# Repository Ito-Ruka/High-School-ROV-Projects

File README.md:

# High-Current ESC Carrier & Power Distribution Board

<p align="center">
  <em>A dedicated power distribution and signal routing carrier designed for Blue Robotics Basic ESCs driving T200 Thrusters.</em>
</p>

---

### Overview

This carrier board consolidates discrete motor controllers into an integrated, serviceable module inside tight electronics enclosures. It pairs high-current DC bus routing with low-noise signal channels to eliminate wire harness congestion and streamline thruster maintenance.

* **Primary Application:** Power distribution and PWM signal breakout for up to 6 external ESCs
* **Target Hardware:** Blue Robotics Basic ESC / T200 Thruster systems
* **Design Toolchain:** KiCad 10.0 Native

---

### Key Architectural Features

* **Integrated ESC Mounting:** Mechanically aligns and retains up to 6 discrete ESC modules into a rigid, compact frame.
* **Optimized Thermal Spreading:** Heavy copper planes provide massive thermal mass and heat dissipation across the substrate during sustained loads.
* **Clean Harness Management:** Groups power taps and signal headers to decouple propulsion wiring from sensitive telemetry lines.
* **Dedicated Auxiliary Port:** Supplies clean parallel DC power for onboard sensors, logic, or auxiliary payloads.

---

### Visual Reference

<table>
  <tr>
    <td width="50%" align="center">
      
      <br><strong>Top Layer & Component Layout</strong>
    </td>
    <td width="50%" align="center">
      
      <br><strong>Bottom Layer & Ground Plane</strong>
    </td>
  </tr>
</table>

---

### Electrical & Mechanical Specifications

| Parameter | Specification | Design Notes |
| :--- | :--- | :--- |
| **Operating Voltage** | 12 V DC | Nominal battery bus input |
| **Max Continuous Current** | 20 A total | Sized for sustained multi-thruster runs |
| **Per-Channel Allocation** | 3 A per ESC channel | Dedicated rail routing for 6 ESC positions |
| **Auxiliary Power Rail** | 2 A continuous capacity | Dedicated breakout for accessories/sensors |
| **Board Dimensions** | 159 mm × 128 mm × 1.6 mm | Landscape $(W \times H \times T)$ footprint |
| **Layer Count** | 2-Layer FR4 | Standard fab; aluminum backing compatible |
| **Copper Weight** | 15 oz/ft² ($525\ \mu\text{m}$) | Extreme heavy copper power distribution |

---

### Fabrication & Assembly Notes (15 oz Copper)
* **Etch Clearance:** Minimum trace clearance and spacing set to $\ge 1.2\text{ mm}$ ($50\text{ mil}$) to prevent shorts from chemical undercut during $525\ \mu\text{m}$ copper etching.

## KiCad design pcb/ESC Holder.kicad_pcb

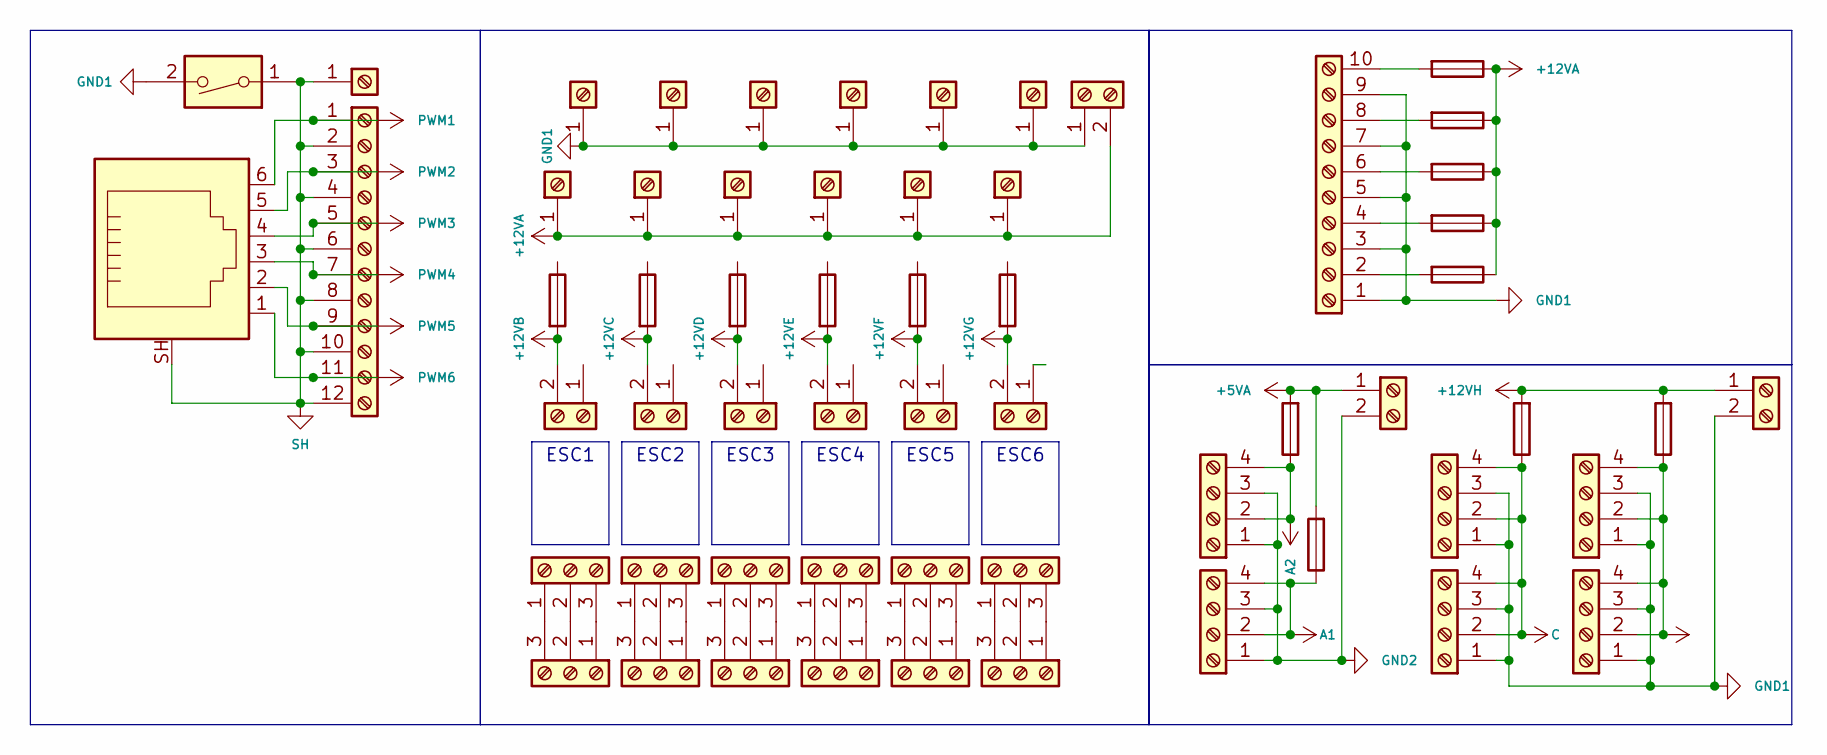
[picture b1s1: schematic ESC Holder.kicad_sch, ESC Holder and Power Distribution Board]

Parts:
F1, F2, F3, F4, F5, F6, F7, F8, F9, F10, F11, F12, F13, F14, F15: Fuse; Fuse Holder 30 A 500V 1 Circuit Blade (FUSE_3568-15)
J1, J6, J9, J12, J15, J18, J22, J28, J43: Screw_Terminal_01x02; 2 Position Wire to Board Terminal Block Horizontal with Boa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
J2, J3, J4, J5, J7, J8, J10, J11, J13, J14, J16, J17: Screw_Terminal_01x03; 3 Position Wire to Board Terminal Block Horizontal with Boa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
J19: RJ12_Shielded; Jack Modular Connector 6p6c (RJ11, RJ12, RJ14, RJ25) 90° An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
J20: Screw_Terminal_01x10; 10 Position Wire to Board Terminal Block Horizontal with Bo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
J21, J27, J29, J30, J31, J32, J33, J34, J35, J36, J37, J38, J39: Screw_Terminal_01x01; 1 Position Wire to Board Terminal Block Horizontal with Boa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
J23, J25, J26, J40, J41, J42: Screw_Terminal_01x04; TERM BLK 4POS SIDE ENTRY 5MM SMD (CONN4_710304_WRE)
J24: Screw_Terminal_01x12; 12 Position Wire to Board Terminal Block Vertical with Boar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
SW1: SW_DIP_x01; SWITCH SLIDE DIP SPST 0.025A 24V (SW_A6TN-1104_OMR)

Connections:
+5VA: F12.2, F15.2, J43.1
+12VA: F2.1, F3.1, F4.1, F5.1, F9.1, J21.1, J22.2, J29.1, J30.1, J31.1, J32.1, J33.1
+12VB: F10.2, J1.2
+12VC: F1.2, J6.2
+12VD: F11.2, J9.2
+12VE: F7.2, J12.2
+12VF: F8.2, J15.2
+12VG: F6.2, J18.2
+12VH: F13.2, F14.2, J28.1
A1: F15.1, J25.2, J25.4
A2: F12.1, J26.2, J26.4
B: F14.1, J41.2, J41.4, J42.2, J42.4
C: F13.1, J23.2, J23.4, J40.2, J40.4
GND1: J20.1, J20.3, J20.5, J20.7, J20.9, J22.1, J23.1, J23.3, J28.2, J34.1, J35.1, J36.1, J37.1, J38.1, J39.1, J40.1, J40.3, J41.1, J41.3, J42.1, J42.3, SW1.2
GND2: J25.1, J25.3, J26.1, J26.3, J43.2
unnamed: J2.1, J3.3
unnamed: J2.2, J3.2
unnamed: J2.3, J3.1
unnamed: J4.1, J5.3
unnamed: J4.2, J5.2
unnamed: J4.3, J5.1
unnamed: J7.1, J8.3
unnamed: J7.2, J8.2
unnamed: J7.3, J8.1
unnamed: J10.1, J11.3
unnamed: J10.2, J11.2
unnamed: J10.3, J11.1
unnamed: J13.1, J14.3
unnamed: J13.2, J14.2
unnamed: J13.3, J14.1
unnamed: J16.1, J17.3
unnamed: J16.2, J17.2
unnamed: J16.3, J17.1
unnamed: F4.2, J20.2
unnamed: F2.2, J20.4
unnamed: F9.2, J20.6
unnamed: F5.2, J20.8
unnamed: F3.2, J20.10
PWM1: J19.6, J24.1
PWM2: J19.5, J24.3
PWM3: J19.4, J24.5
PWM4: J19.3, J24.7
PWM5: J19.2, J24.9
PWM6: J19.1, J24.11
SH: J19.SH, J24.2, J24.4, J24.6, J24.8, J24.10, J24.12, J27.1, SW1.1

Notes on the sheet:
ESC4
ESC1
ESC3
ESC2
ESC6
ESC5

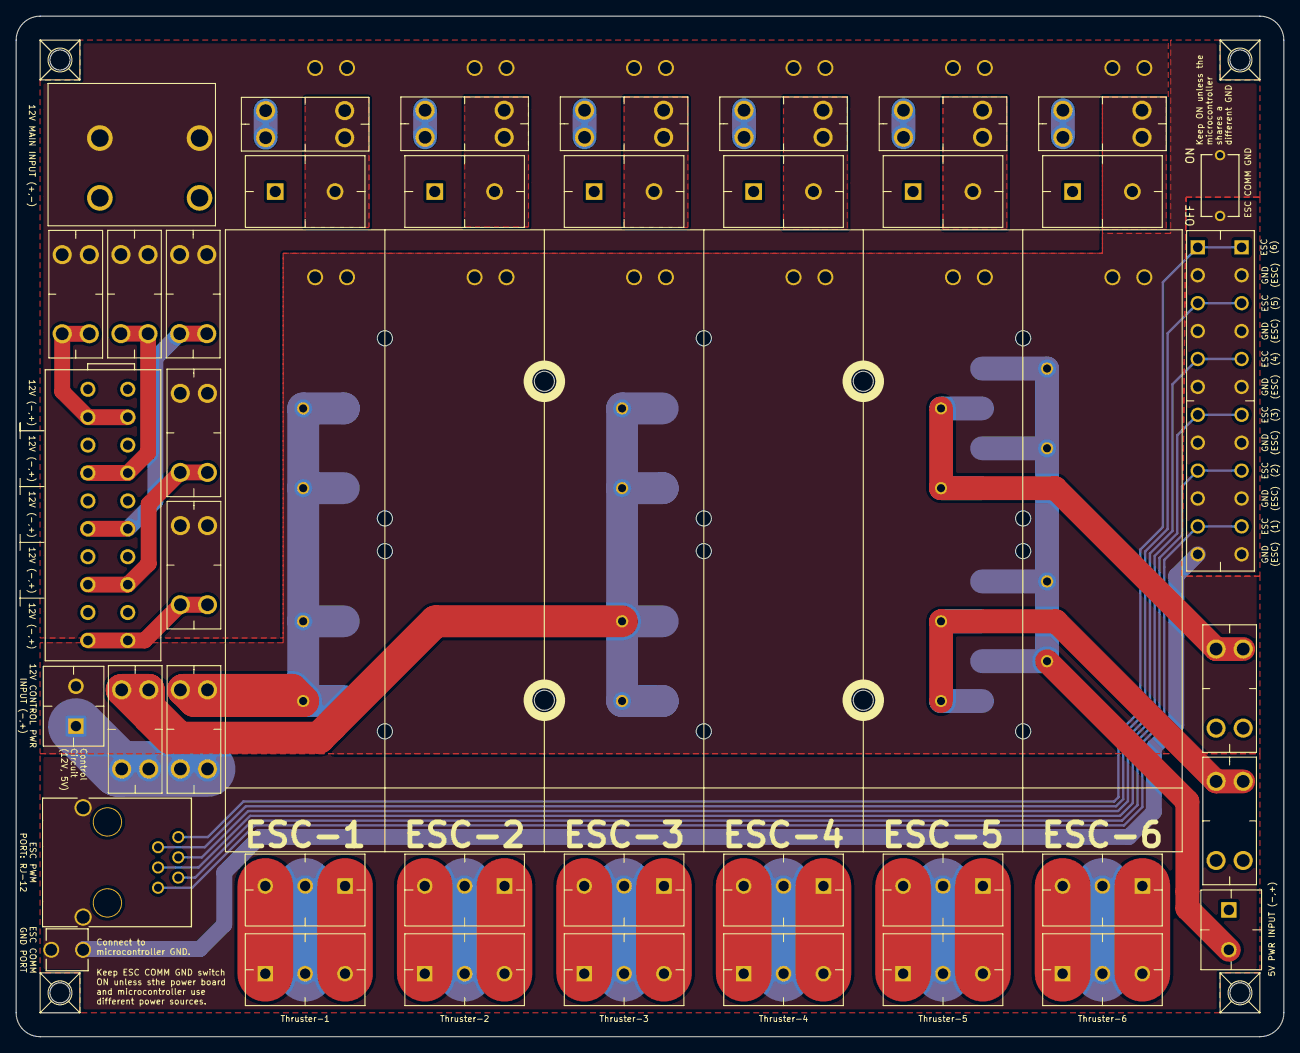
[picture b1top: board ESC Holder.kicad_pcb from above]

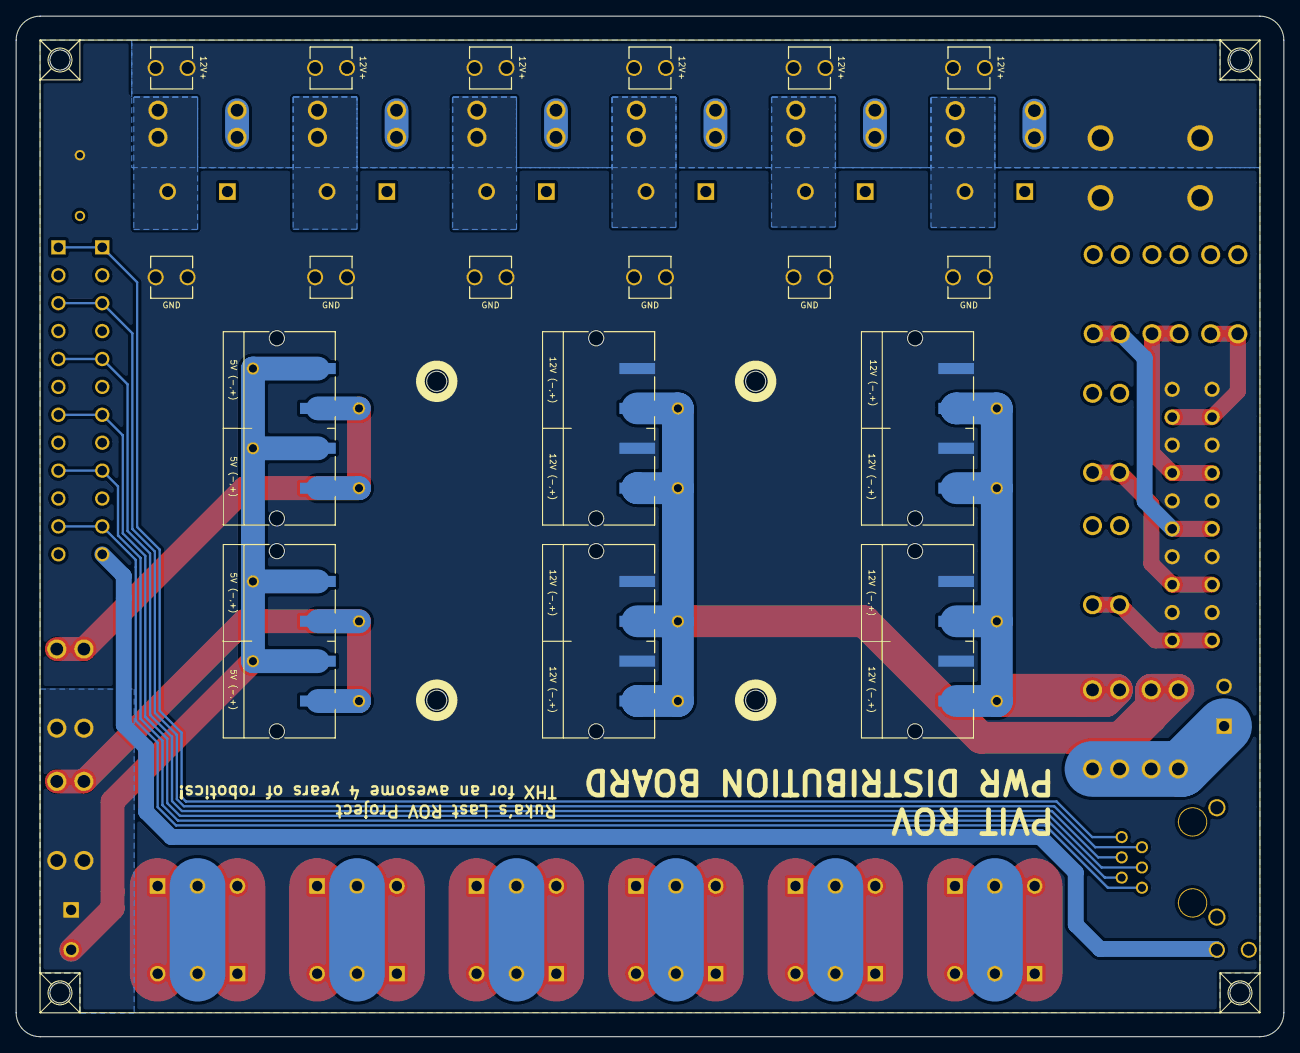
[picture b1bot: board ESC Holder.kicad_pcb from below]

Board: 2 copper layers, 159.0 x 128.0 mm, 59 parts (18 on the bottom side), 45 nets.
